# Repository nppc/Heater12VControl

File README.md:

# uReflow Station
Micro Reflow Station with 12V heating ceramic element and temperature PID control.

The device is only 13cm long. Heating plate is 4x4cm. Power is 12VDC.

## 2 modes of operation: Manual and Automatic.
In Manual mode preset temperature is maintained. The temperature can be adjusted on the fly.
In Automatic mode the device is following general reflow thermal profile.

Example of reflow soldering thermal profile (from Wikipedia)

Every parameter can be adjusted (Soak and reflow temperature and time). Preset can be configured and stored in EEPROM and can be adjusted on the fly.

### We will need:
- 1 Heating element like XD-JR80 12V48W
- 1 Thermistor 100K NTC 3950 (from 3D printer)
- 1 Arduino Nano
- 1 Rotary Encoder like EC11
- 1 OLED 128x32 with I2c
- 1 P-Mosfet like AON6403, AON6411, AON7423 or similar.
- And some other smd components
- PCB from OSHPark: https://oshpark.com/shared_projects/yKbu7gQC

I have added to the firmware support for K type thermocouple (MAX31855 or MAX6675), but made no PCB for this. I left it up to your creativity. :)

Controller board (OLED, rotary encoder, mosfet control and thermistor monitor):

## LCD screens snapshots:
### Start menu 
(choose two presets - manual temperature regulation or automatic reflow)

### Manual mode 
- Target temperature is adjustable on the fly. 
- Timer is counting total time while on target temperature.

### Automatic Reflow mode
- Indication of current step (soak, reflow, cooling)
- Timer for every step
- Target temperature and time is adjustable on the fly. 

(Ramp to soak step)

(Soak step - preheating)

(Ramp to reflow step)

(Reflow step)

(Cooling down step)

## Configurable parameters
(long button press while in start menu)
- PID P
- PID I
- PID D
- Soak temperature (preheating)
- Soak time (preheating)
- Reflow temperature
- Reflow time
- Target temperature for Manual mode

## Compiling with Arduino
You can use latest Arduino IDE.
And need to include two libraries via Arduino IDE Libraries Manager

Discussion here: https://www.rcgroups.com/forums/showthread.php?2998269-DIY-reflow-soldering-ceramic-plate

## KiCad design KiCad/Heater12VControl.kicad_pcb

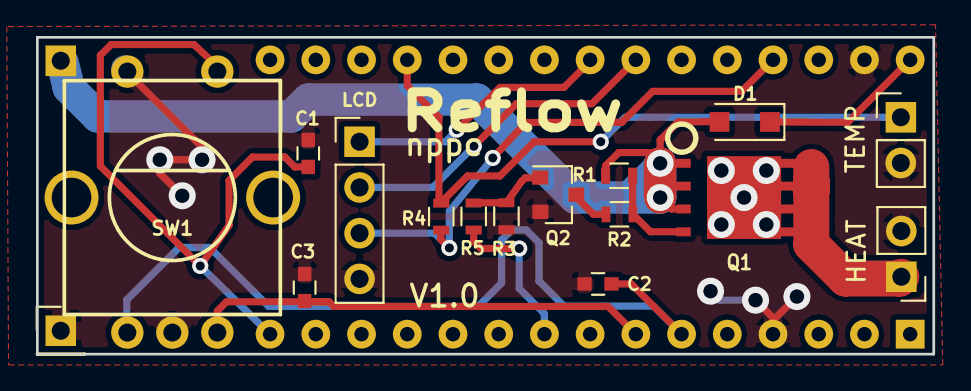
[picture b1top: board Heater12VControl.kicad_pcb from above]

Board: 2 copper layers, 49.8 x 17.6 mm, 18 parts (1 on the bottom side), 15 nets.

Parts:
12V: PWR; Pin_Header_Straight_1x01_Pitch2.54mm
C1, C2, C3: 22n; C_0603
D1: D; D_SOD-123F
GND: PWR; Pin_Header_Straight_1x01_Pitch2.54mm
HEAT: Heater; Pin_Header_Straight_1x02_Pitch2.54mm
J4: Arduino_Nano_Header; Arduino_Nano
LCD: LCD; Pin_Header_Straight_1x04_Pitch2.54mm
Q1: AON6403; DFN-8-1EP_6x5mm
Q2: SI2308; SOT-23
R1: 100K; R_0603
R2: 1K; R_0603
R3: 10K; R_0603
R4: 4.7K; R_0603
R5: 100; R_0603
SW1: Rotary_Encoder; ROTARY-ENCODER
TEMP: Temp sensor; Pin_Header_Straight_1x02_Pitch2.54mm

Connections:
+12V: 12V.1, D1.2, Q1.3, R1.1
/Heat: J4.9, R5.1
/Temp: J4.19, R4.1, TEMP.1
GND: C1.2, C2.2, C3.2, GND.1, HEAT.2, J4.4, J4.29, LCD.4, Q2.2, R3.2, SW1.2, SW1.4, TEMP.2
unnamed: C1.1, J4.15, SW1.5
unnamed: C2.1, J4.6, SW1.1
unnamed: C3.1, J4.7, SW1.3
unnamed: D1.1, J4.30
unnamed: HEAT.1, Q1.2
unnamed: J4.23, LCD.1
unnamed: J4.24, LCD.2
unnamed: Q1.1, R1.2, R2.1
unnamed: Q2.1, R3.1, R5.2
unnamed: Q2.3, R2.2
VCC: J4.27, LCD.3, R4.2

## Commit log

2017-09-28 Firmware alfa version with POT
2017-09-29 some measurements done
2017-10-02 Temperature table adjusted
2017-11-24 Finished version with Display
2017-12-01 New Version with rotary encoder and AIO pcb
2017-12-04 added images
2017-12-04 MOve images
2017-12-11 in progress...
2017-12-18 A bit of progress with Config menu
2017-12-21 Draft version implemented settings menu
2017-12-22 First draft version with manual mode (not tested)
2017-12-27 Timer control in Manual Mode
2017-12-27 More debug output added
2017-12-28 More Debug added. Some improvements in Encoder handling.
2017-12-28 PCB Image added
2017-12-28 Added experimental Graphical Logger
2017-12-31 Adjust PID range and values
2018-01-01 Small cosmetic changes
2018-01-01 Fix bug with no sensor detection
2018-01-01 Adjust Logger. Freeup SRAM
2018-01-02 Added Automatic Mode
2018-01-02 Readme adjust
2018-01-17 Fixed Main and Configuration screen
2018-01-18 Fixed major grphics bugs
2018-01-18 LCD snapshots added. Small code adjustments
2018-01-18 Small cosmetic adjustments
2018-01-18 Small cosmetic adjustments 2
2018-01-18 Images updated
2018-01-18 Configure target temperature for Manual mode
2018-01-18 Adjust no sensor detection
2018-01-19 Quite working version. Can be released.
2018-01-19 Add logger as permanent feature in Manual mode
2018-01-19 Start SCAD project for Heater box
2018-01-19 Added temperature to main menu.
2018-01-21 Add OpenScad project
2018-01-22 Final SCAD project. Box is ready
2018-01-23 Some photos added
2018-01-24 First firmware release
2018-01-24 Source code cleanup - only cosmetic look of the code
2018-01-25 Add workaround for broken bootloader in some Arduinos
2018-01-29 Added some images
2018-01-29 Add some more details
2018-01-30 Added link to RcGroups
2018-03-27 BOM added
2018-03-27 BOM added Q2
2018-03-28 Schematic PDF added
2018-03-28 MOsfet Alternative added
2018-03-29 Added support for MAX31855 and MAX6675
2018-03-29 MAX pin assignment changed
2018-04-06 Added compiling info
2018-08-18 Added support for Fan on Cooling stage
2018-08-18 Counter can run in seconds or minutes
2018-08-18 Adjusted config menu for minutes counter
2019-04-29 Fixed TIMER_DIVIDER define
2019-04-29 cleanup the code. exit to menu after finishing auto mode
2021-03-03 Update HeaterControlV2.ino
    Fix 32bit math calculation
2021-03-03 Update HeaterControlV2.ino
    make sure define will be used correctly
2021-03-03 Fix minutes (slow) counter
